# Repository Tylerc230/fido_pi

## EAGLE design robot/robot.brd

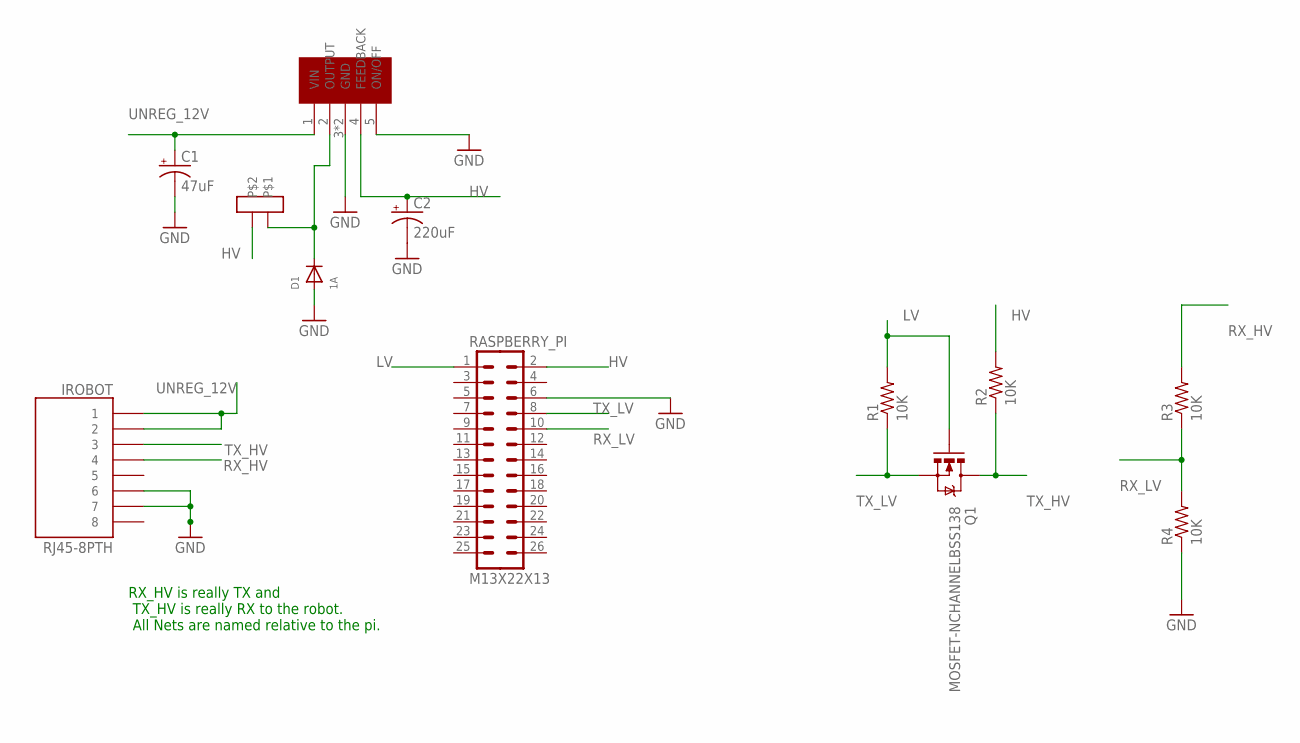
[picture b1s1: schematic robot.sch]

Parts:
C1: 47uF; PANASONIC_D
C2: 220uF; PANASONIC_D
D1: 1A; SOD-123
IROBOT: RJ45-8PTH; RJ45-8
Q1: MOSFET-NCHANNELBSS138; SOT23
R1, R2, R3, R4: 10K; 0805
RASPBERRY_PI: M13X22X13; 2X13
U$1: TL2575; TO-263
U$2: PE-52627NL

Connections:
GND: C1.-, C2.-, D1.A, IROBOT.6, IROBOT.7, R4.1, RASPBERRY_PI.6, U$1.3 (GND), U$1.5 (ON/OFF), U$1.6 (GND)
HV: C2.+, R2.2, RASPBERRY_PI.2, U$1.4 (FEEDBACK), U$2.P$2
LV: Q1.1 (G), R1.2, RASPBERRY_PI.1
unnamed: D1.C, U$1.2 (OUTPUT), U$2.P$1
RX_HV: IROBOT.4, R3.2
RX_LV: R3.1, R4.2, RASPBERRY_PI.10
TX_HV: IROBOT.3, Q1.3 (D), R2.1
TX_LV: Q1.2 (S), R1.1, RASPBERRY_PI.8
UNREG_12V: C1.+, IROBOT.1, IROBOT.2, U$1.1 (VIN)

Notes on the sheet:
RX_HV is really TX and TX_HV is really RX to the robot. All Nets are named relative to the pi.

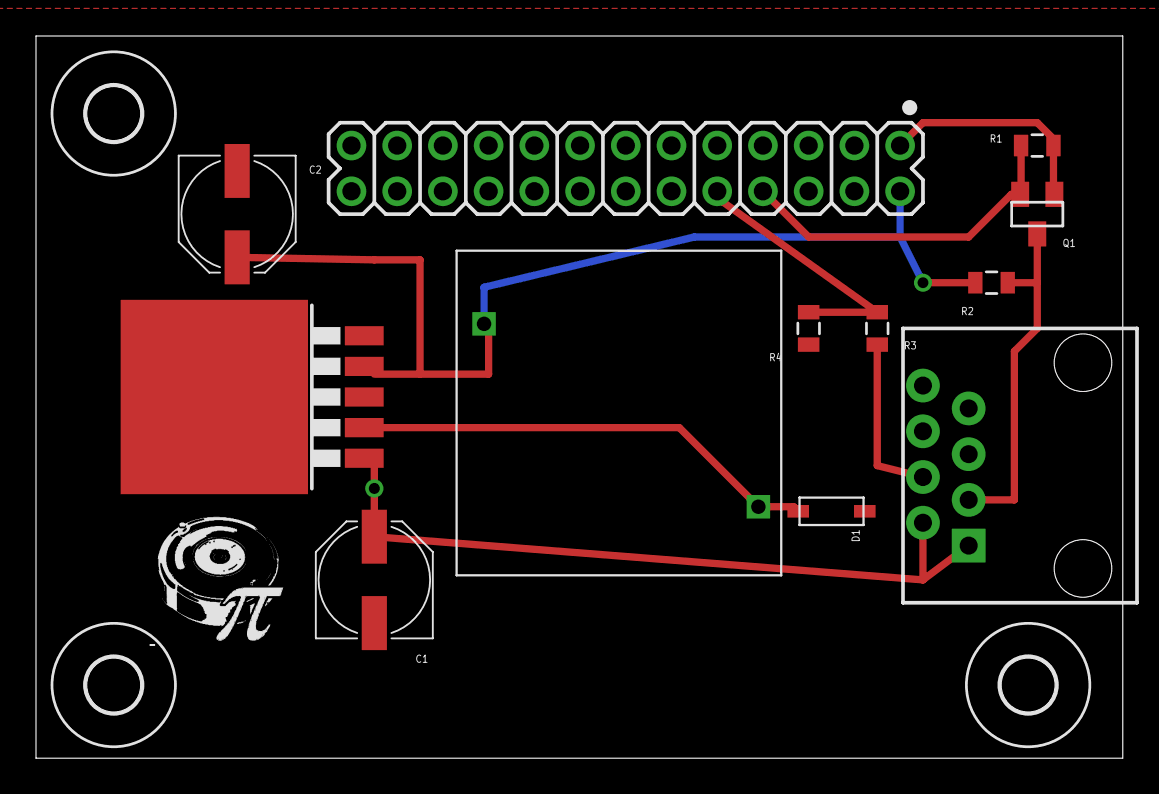
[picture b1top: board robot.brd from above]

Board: 2 copper layers, 60.4 x 40.1 mm, 15 parts (0 on the bottom side), 9 nets.

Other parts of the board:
U$3, U$5, U$6: 3,0

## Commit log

2013-03-01 Initial import of fido project from svn
2013-03-01 Add a serial.py file that works on raspberry pi
    This is a drop in replacement for pySerial that wraps wiringPi
    interface.
2013-03-01 Add readme
2013-03-05 Add sync script to rsync files to pi
    I do this so I don't have to do dev on the pi. Its slow.
2013-03-05 Auto sync all files to pi when I save a buffer
    This uses per folder .exrc file and an autocommand to rsync everything.
2013-03-12 Sync the web interface portion of the app to web2py application folder
    We sync the web2py application which implements the web interface of our
    robot to the web2py install dir on the pi
2013-03-12 We aren't using web_ui gsd web server
    The web_ui server interface should be deleted at some point.
2013-03-12 Starts the xmlrpc server on port 9000
    We've also included a client to test the connection.
2013-03-12 Add a simple web interface for controlling the robot
    This was copied from the arduino project.
2013-03-14 Use proper baud and device for pi serial
    baud == 115200 and device = /dev/ttyAMA0
2013-03-14 Need to make Control() call on roomba before we can move it
    This is in the rpc server which sits and waits for other processes to
    make calls to it.
2013-03-14 Web interface making proper calls to rpc server
    The browser client makes calls back to the robot.py controller which
    then makes calls to the rpc server
2013-03-14 Create one script to start web server and rpc server
2013-03-14 New script to test pyrobot functionality
    Robot should be connected when this script runs
2013-03-14 Run start as sudo sh ./start.sh
2013-03-25 Change sync command to use wifi address instead of ethernet
    Just changed the hard coded wifi ip
2013-04-15 Serve web page via wireless interface
2013-04-15 Adjust the forward and back speed
2013-04-16 Remove files from fido project
    These files were part of the olpc fido project which were not using.
2013-04-18 Use flask instead of web2py
    Flask is a much more lightweight framework and more suited to pi.
2013-06-13 Push code to pi_fido in root
    We now just keep all of the robot code in pi_fido on the target device.
2013-06-15 Turn of auto sync for now
2013-06-15 Start using flash instead of web2py
    We also write the current pid to a file.
2013-06-16 Start server from python script
    We are going to use a python script to start all the various servers as
    bash is difficult.
2013-06-16 Fork the web interface into a separate process
    We have several processes that we want to start for the complete robot.
    We need the hardware interface, the web interface and the camera
    interface.
2013-06-16 Remove old bash start script
2013-06-16 Move roomba related code into its own subfolder
    We will have subfolders for all the major portions of the system (web
    interface, roomba control and camera control).
2013-06-16 Add __init__ files to all sub dirs to be imported
2013-06-17 Start roomba interface process
    We fork the xmlrpc server to allow communication between the roomba and
    the web interface.
2013-06-20 Sync script cleans up old files on pi
    We use the delete flag to clean up files which have been deleted
    locally.
2013-06-20 Add camera interface to system
    We are using the pi still camera command line app and the mjpg streaming
    app to allow us to stream stills to a webpage.
2013-08-16 Add eagle files to project
    These are the eagle files for producing a PCB which adds better power
    consumption and converts the serial from 3v3 to 5 volts.
2013-08-21 Cleaning up the pcb
2013-08-21 Made board shorter
2013-08-23 Add drill holes and graphic

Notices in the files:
parts and their libraries:
SparkFun-Capacitors: Licensing: CC v3.0 Share-Alike You are welcome to use this library for commercial purposes.
